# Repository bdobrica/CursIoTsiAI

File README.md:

# CursIoTsiAI
Repo pentru Cursul de Internet of Things și Inteligență Artificială

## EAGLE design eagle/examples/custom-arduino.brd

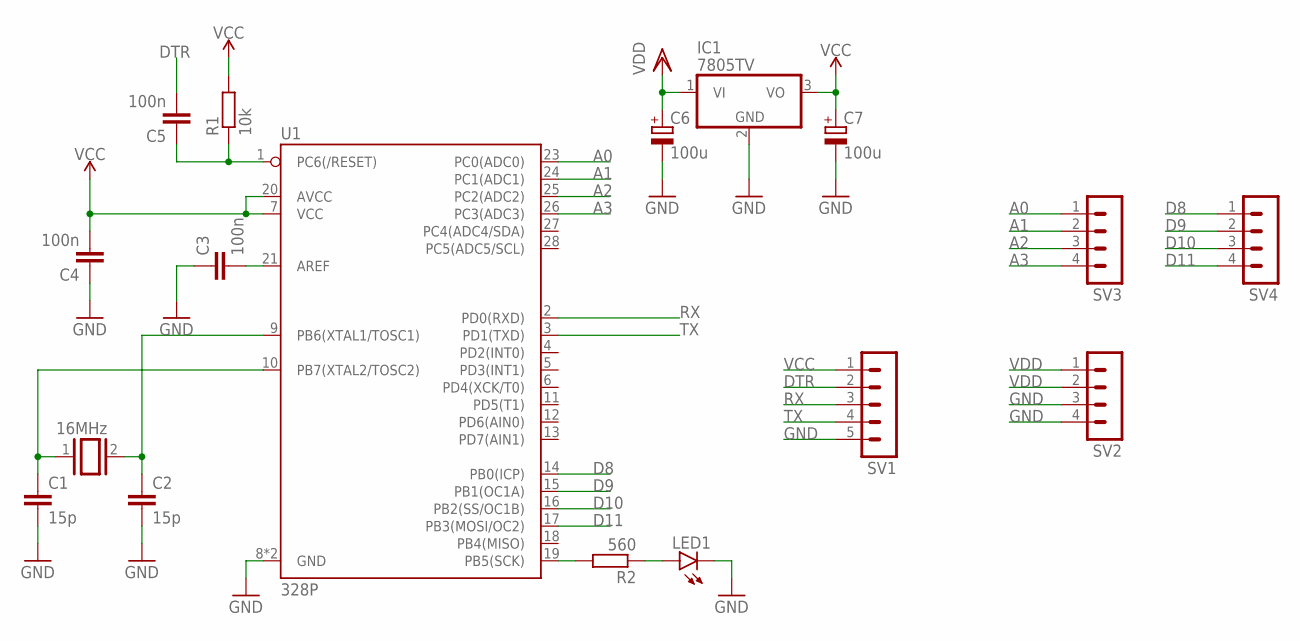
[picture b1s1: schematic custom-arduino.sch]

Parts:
C1, C2: 15p; C025-024X044
C3, C4, C5: 100n; C025-024X044
C6, C7: 100u; E2,5-7
IC1: 7805TV; TO220V
LED1: LED5MM
Q1: 16MHz; QS
R1: 10k; 0207/10
R2: 560; 0207/10
SV1: MA05-1
SV2, SV3, SV4: MA04-1
U1: 328P; DIP28

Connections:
A0: SV3.1, U1.23 (PC0(ADC0))
A1: SV3.2, U1.24 (PC1(ADC1))
A2: SV3.3, U1.25 (PC2(ADC2))
A3: SV3.4, U1.26 (PC3(ADC3))
D8: SV4.1, U1.14 (PB0(ICP))
D9: SV4.2, U1.15 (PB1(OC1A))
D10: SV4.3, U1.16 (PB2(SS/OC1B))
D11: SV4.4, U1.17 (PB3(MOSI/OC2))
DTR: C5.2, SV1.2
GND: C1.2, C2.2, C3.1, C4.1, C6.-, C7.-, IC1.2 (GND), LED1.K (C), SV1.5, SV2.3, SV2.4, U1.8 (GND), U1.22 (GND)
unnamed: C3.2, U1.21 (AREF)
unnamed: C5.1, R1.1, U1.1 (PC6(/RESET))
unnamed: R2.2, U1.19 (PB5(SCK))
unnamed: LED1.A, R2.1
unnamed: C2.1, Q1.2, U1.9 (PB6(XTAL1/TOSC1))
unnamed: C1.1, Q1.1, U1.10 (PB7(XTAL2/TOSC2))
RX: SV1.3, U1.2 (PD0(RXD))
TX: SV1.4, U1.3 (PD1(TXD))
VCC: C4.2, C7.+, IC1.3 (VO), R1.2, SV1.1, U1.7 (VCC), U1.20 (AVCC)
VDD: C6.+, IC1.1 (VI), SV2.1, SV2.2

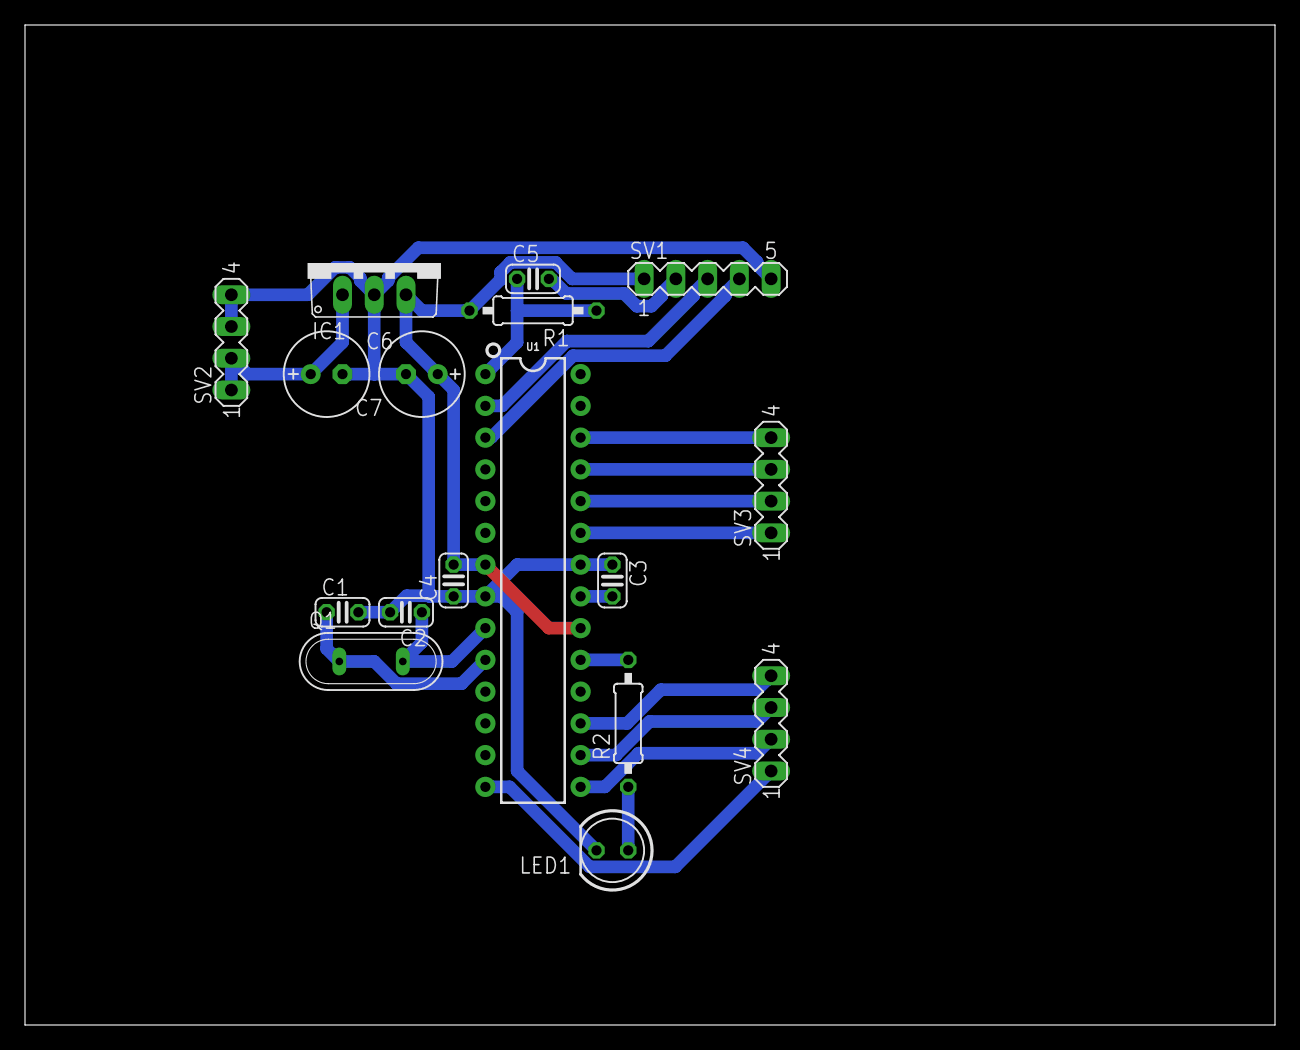
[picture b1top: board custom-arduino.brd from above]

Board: 2 copper layers, 100.0 x 80.0 mm, 17 parts (0 on the bottom side), 20 nets.

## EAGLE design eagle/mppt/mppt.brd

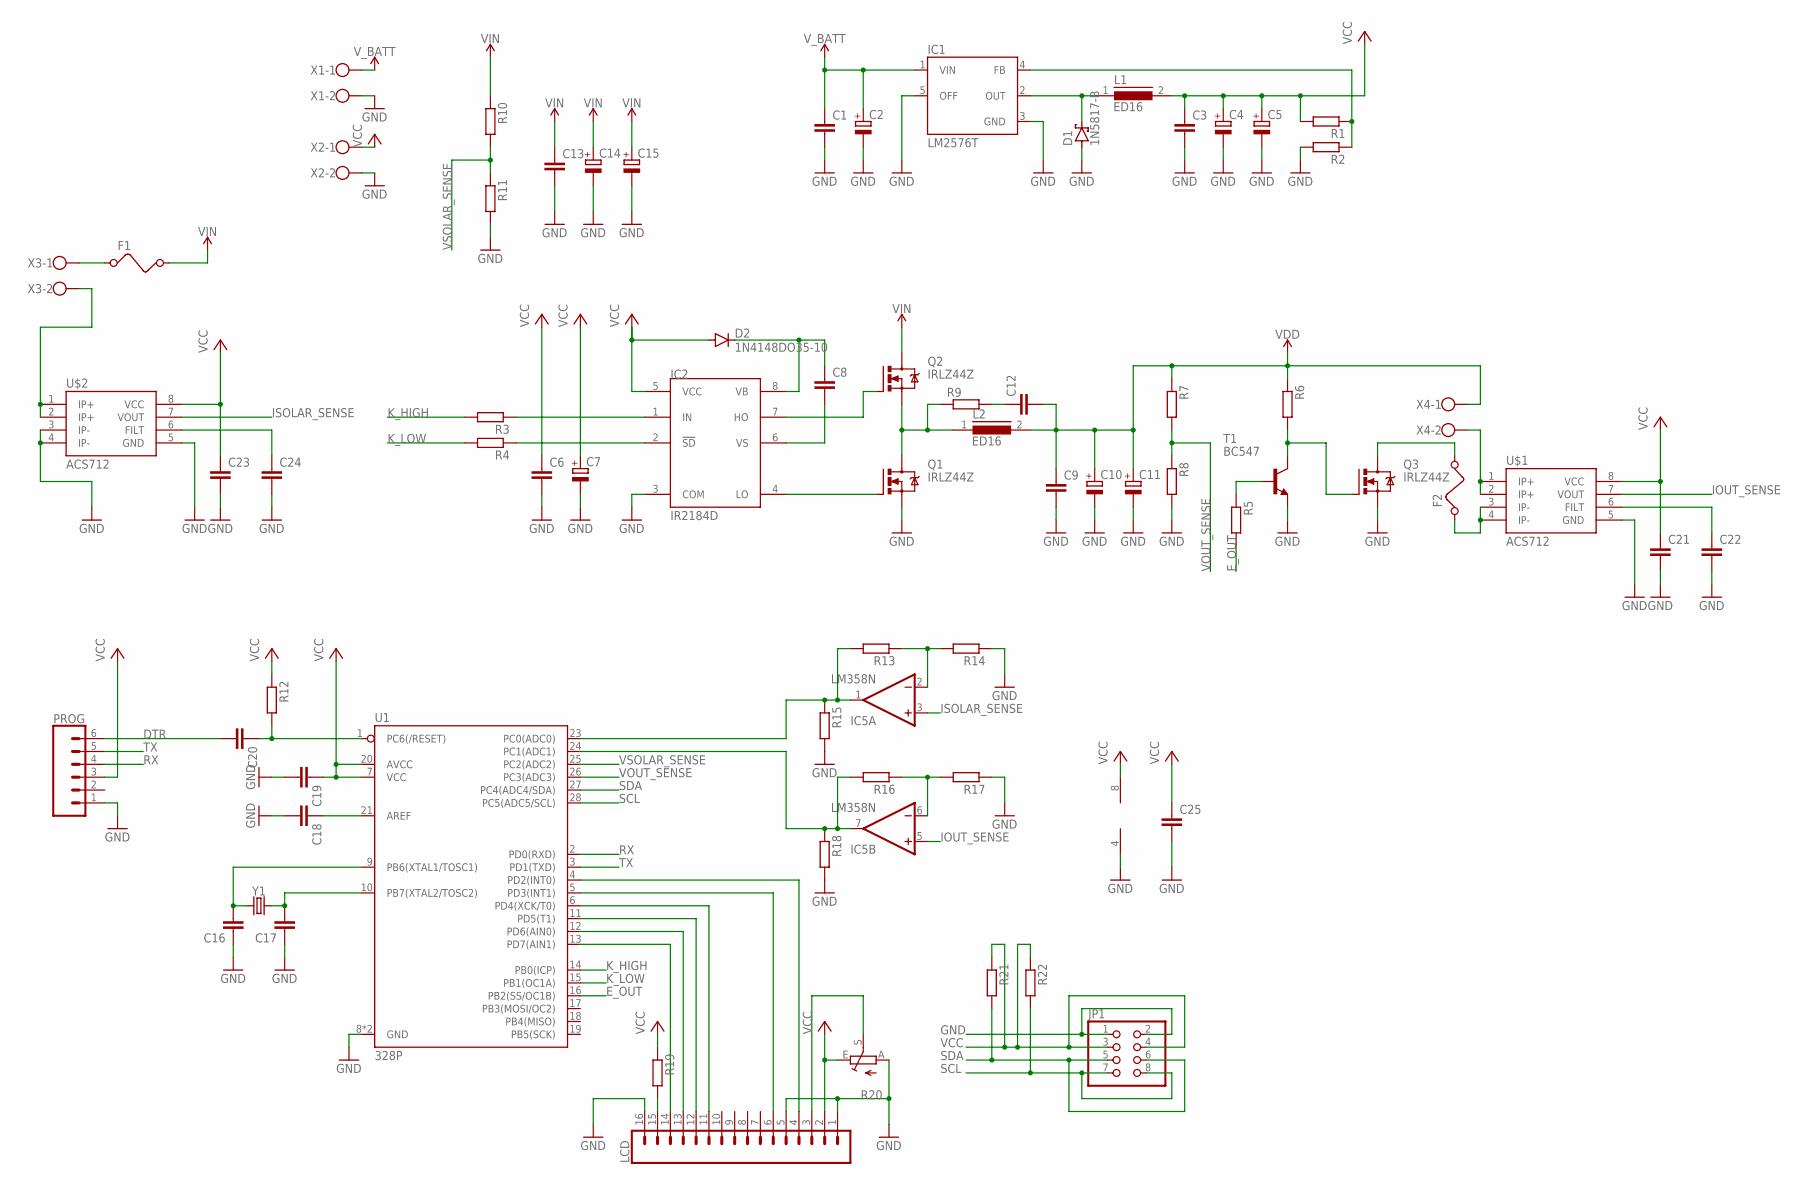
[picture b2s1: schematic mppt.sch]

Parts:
C1, C3, C6, C8, C9, C12, C13, C16, C17, C18, C19, C20, C21, C22, C23, C24, C25: C-EU025-024X044; C025-024X044
C2, C4, C5, C7: CPOL-EUE5-6; E5-6
C10, C11, C14, C15: CPOL-EUE7.5-16; E7,5-16
D1: 1N5817-B; DO41-7.6
D2: 1N4148DO35-10; DO35-10
F1, F2: FUSE
IC1: LM2576T; TO220-5
IC2: IR2184D; DIL08
IC5: LM358N; DIL08
JP1: PINHD-2X4; 2X04
L1, L2: ED16
LCD: CONN_16LONGPADS; 1X16_LONGPADS
PROG: CONN_06LONGPADS; 1X06_LONGPADS
Q1, Q2, Q3: IRLZ44Z; TO220BH
R1, R2, R3, R4, R5, R6, R7, R8, R9, R10, R11, R12, R13, R14, R15, R16, R17, R18, R19, R21, R22: R-EU_0207/10; 0207/10
R20: TRIM_EU-B64Y; B64Y
T1: BC547; TO92
U1: 328P; DIP28
U$1, U$2: ACS712; SO08
X1, X2, X3, X4: W237-102
Y1: CRYSTALPTH-HC49UV; HC49U

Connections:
DTR: C20.2, PROG.6
E_OUT: R5.2, U1.16 (PB2(SS/OC1B))
GND: C1.2, C2.-, C3.2, C4.-, C5.-, C6.2, C7.-, C9.2, C10.-, C11.-, C13.2, C14.-, C15.-, C16.1, C17.1, C18.2, C19.2, C21.2, C22.2, C23.2, C24.2, C25.2, D1.A, IC1.3 (GND), IC1.5 (OFF), IC2.3 (COM), IC5.4 (V-), JP1.1, JP1.2, LCD.1, LCD.5, LCD.16, PROG.1, Q1.S, Q3.S, R2.2, R8.2, R11.2, R14.1, R15.2, R17.1, R18.2, R20.A, T1.1 (E), U1.8 (GND), U1.22 (GND), U$1.5 (GND), U$2.3 (IP-), U$2.4 (IP-), U$2.5 (GND), X1.2, X2.2
IOUT_SENSE: IC5.5 (+IN), U$1.7 (VOUT)
ISOLAR_SENSE: IC5.3 (+IN), U$2.7 (VOUT)
K_HIGH: R3.2, U1.14 (PB0(ICP))
K_LOW: R4.2, U1.15 (PB1(OC1A))
unnamed: L2.1, Q1.D, Q2.S, R9.1
unnamed: D1.C, IC1.2 (OUT), L1.1
unnamed: IC2.7 (HO), Q2.G
unnamed: IC1.4 (FB), R1.1, R2.1
unnamed: IC2.4 (LO), Q1.G
unnamed: IC5.1 (OUT), R13.2, R15.1, U1.23 (PC0(ADC0))
unnamed: IC2.1 (IN), R3.1
unnamed: IC2.2 (!SD), R4.1
unnamed: R5.1, T1.2 (B)
unnamed: Q3.G, R6.2, T1.3 (C)
unnamed: C22.1, U$1.6 (FILT)
unnamed: F2.2, Q3.D
unnamed: LCD.15, R19.2
unnamed: IC5.7 (OUT), R16.2, R18.1, U1.24 (PC1(ADC1))
unnamed: C24.1, U$2.6 (FILT)
unnamed: C16.2, U1.9 (PB6(XTAL1/TOSC1)), Y1.1
unnamed: C12.1, R9.2
unnamed: C17.2, U1.10 (PB7(XTAL2/TOSC2)), Y1.2
unnamed: C20.1, R12.2, U1.1 (PC6(/RESET))
unnamed: U$2.1 (IP+), U$2.2 (IP+), X3.2
unnamed: F1.1, X3.1
unnamed: C18.1, U1.21 (AREF)
unnamed: F2.1, U$1.3 (IP-), U$1.4 (IP-)
unnamed: IC5.2 (-IN), R13.1, R14.2
unnamed: IC5.6 (-IN), R16.1, R17.2
unnamed: LCD.3, R20.S
unnamed: LCD.4, U1.4 (PD2(INT0))
unnamed: LCD.6, U1.5 (PD3(INT1))
unnamed: LCD.11, U1.6 (PD4(XCK/T0))
unnamed: LCD.12, U1.11 (PD5(T1))
unnamed: LCD.13, U1.12 (PD6(AIN0))
unnamed: LCD.14, U1.13 (PD7(AIN1))
unnamed: U$1.1 (IP+), U$1.2 (IP+), X4.2
RX: PROG.4, U1.2 (PD0(RXD))
SCL: JP1.7, JP1.8, R22.2, U1.28 (PC5(ADC5/SCL))
SDA: JP1.5, JP1.6, R21.2, U1.27 (PC4(ADC4/SDA))
TX: PROG.5, U1.3 (PD1(TXD))
VB: C8.1, D2.C, IC2.8 (VB)
VCC: C3.1, C4.+, C5.+, C6.1, C7.+, C19.1, C21.1, C23.1, C25.1, D2.A, IC2.5 (VCC), IC5.8 (V+), JP1.3, JP1.4, L1.2, LCD.2, PROG.3, R1.2, R12.1, R19.1, R20.E, R21.1, R22.1, U1.7 (VCC), U1.20 (AVCC), U$1.8 (VCC), U$2.8 (VCC), X2.1
VDD: C9.1, C10.+, C11.+, C12.2, L2.2, R6.1, R7.1, X4.1
VIN: C13.1, C14.+, C15.+, F1.2, Q2.D, R10.1
VOUT_SENSE: R7.2, R8.1, U1.26 (PC3(ADC3))
VS: C8.2, IC2.6 (VS)
VSOLAR_SENSE: R10.2, R11.1, U1.25 (PC2(ADC2))
V_BATT: C1.1, C2.+, IC1.1 (VIN), X1.1

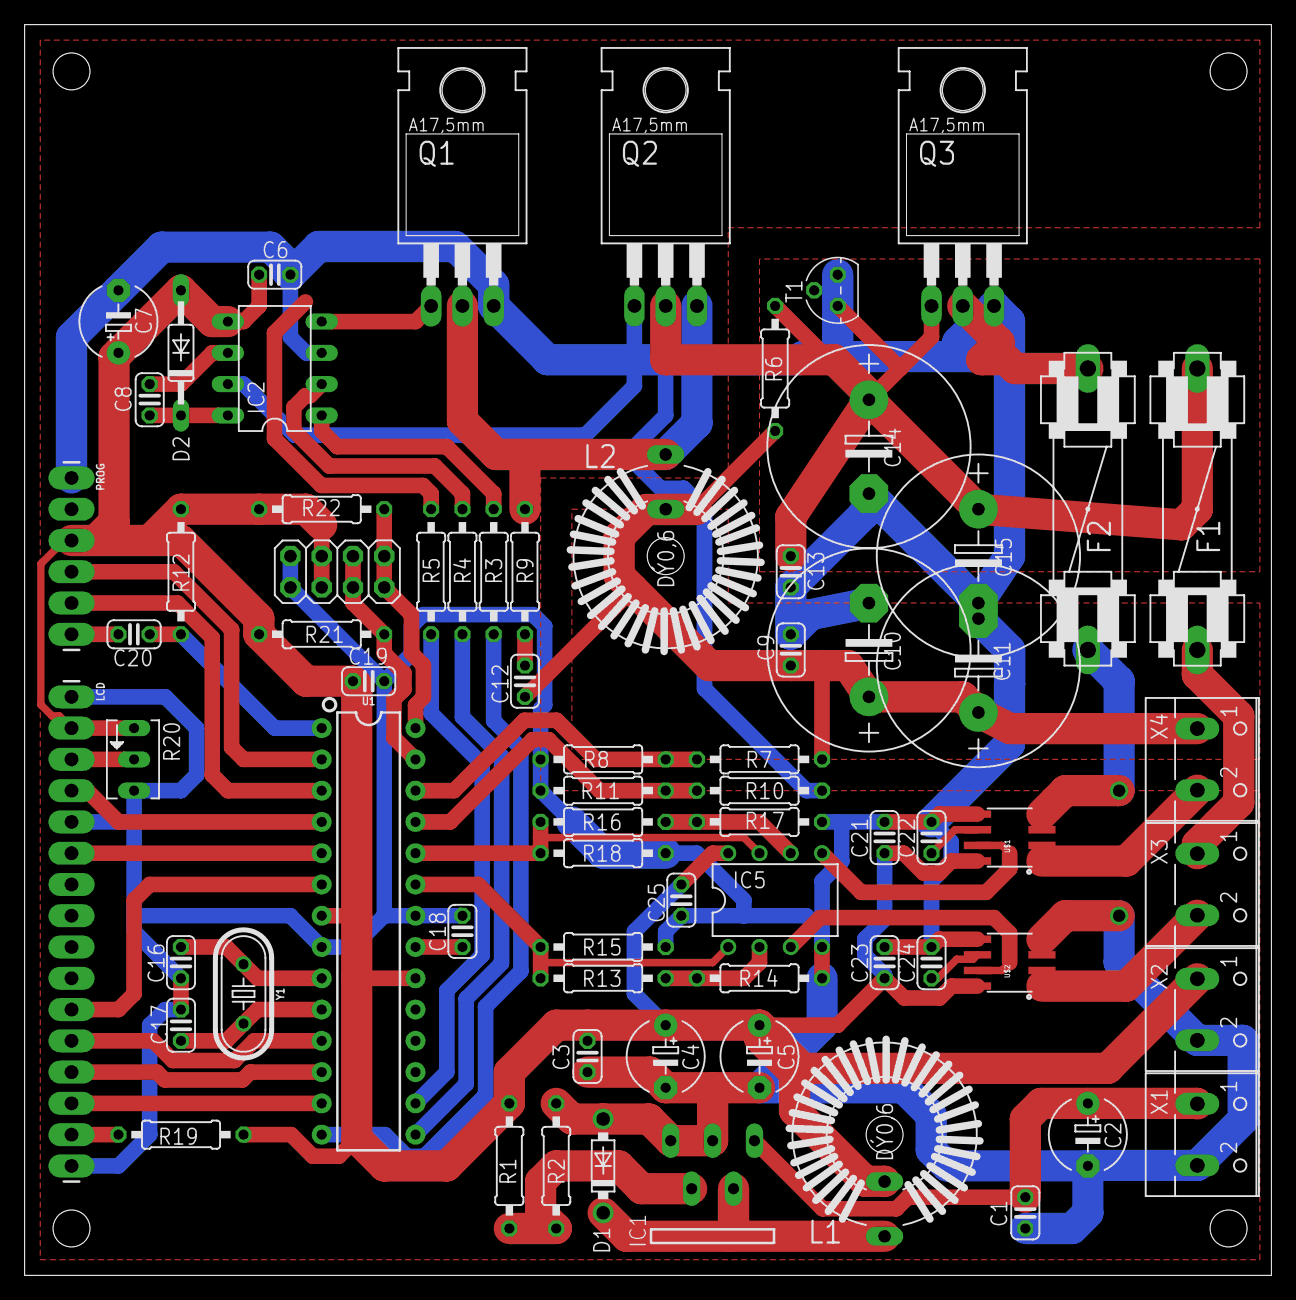
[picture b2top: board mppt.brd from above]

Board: 2 copper layers, 101.3 x 101.6 mm, 71 parts (0 on the bottom side), 52 nets.

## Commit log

2024-03-07 Lecture 01 Update 01
2024-03-08 Lecture 01 Update 02
2024-03-16 CISA-01: Modified Code
    S-a modificat schimbarea
2024-03-16 fix weather station
2024-03-22 Eagle Example Files

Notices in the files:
parts and their libraries:
SparkFun-IC-Microcontroller: Licensing: Creative Commons ShareAlike 4.0 International - https://creativecommons.org/licenses/by-sa/4.0
